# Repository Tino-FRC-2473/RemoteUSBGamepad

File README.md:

# RemoteUSBGamepad

Bridge USB gamepads over IP to enable FTC remote operation

# Client
Download the <a href="https://raw.githubusercontent.com/Tino-FRC-2473/RemoteUSBGamepad/master/client/controller_client.html" download>client page</a> (right click -> Save As) and open in a browser.  The client webpage uses the [Javascript Gamepad API](https://developer.mozilla.org/en-US/docs/Web/API/Gamepad_API), which is sufficiently supported by most modern browsers. 

1. Enter the address and port of the server you wish to connect to.

2. Then connect a gamepad to your computer and press some buttons so the browser can detect it. If you are using the Logitech F310 controller, make sure the switch on the back is set to "D" before plugging it into your computer.

3. Press the Connect button to establish connection to the server

# Server
This project uses pipenv to manage dependencies. Run `pipenv install` on first clone to download and install Python dependencies.

Run server script with `pipenv run python3 server/gamepad_bridge_server.py /dev/serial0`, replacing `/dev/serial0` with the appropriate serial UART for your system. For testing, you can add the `--dummy-serial` option to skip connecting to a physical serial port.

# Firmware
The firmware is written to run on both [Teensy boards](https://www.pjrc.com/teensy/) via the [Teensyduino Joystick API](https://www.pjrc.com/teensy/td_joystick.html) and Arduino boards via the [Arduino XInput library](https://github.com/dmadison/ArduinoXInput). Note that the XInput library requires additional installation procedures, but can run on either Arduino or Teensy boards. Also, XInput is a Microsoft API, so boards running with the XInput library will not be detected as joysticks on Mac or Linux computers without additional software. On an Android phone running the driver station app, XInput devices will appear as Xbox 360 controllers.

# Teensy Carrier Board

The Teensys listen for incoming command on a common serial bus. To simplify connecting all the RX lines together to the Raspberry Pi's serial TX, we designed a simple carrier board. The first design is a single-sided prototype suitable for milling on a desktop CNC machine. Each board holds four Teensy LCs, with headers for ground and serial RX. Note that the Teensys receive power via USB, but share a common ground with the Raspberry Pi. A second set of headers allows these boards to be daisy chained to easily add additional Teensys. The address or device index for each Teensy is programmed using a set of jumpers selective pulling down GPIO pins 2-5. Each Teensy reads its ID as a binary coded number on boot based on the jumper configuration.

# Protocol
The same binary message format will be used over the Websocket and serial connection. We shall use little-endian byte order to match the Arduino/ARM processor convention. All messages start with the following header:

Field | Size (bytes) | Description 
------------ | ------------- | -------------
Index | 1 | ID of destination controller
Command ID | 1 | Numeric identifier signfying message type
Length | 2 | Length of the message body in bytes. Note this does not include this header, only the contents following.

## Connection Start Command (CID=0x00)
Signify that a client has connected to the given controller index. No message body (length = 0).

## Connection End Command (CID=0x01)
Signify that a client has disconnected from the given controller index. No message body (length = 0).

## Controller State Report (CID=0x80)
Report the controller state from client to server/device. Message body:

Field | Size (bytes) | Description 
------------ | ------------- | -------------
Joystick1_X | 2 | Joystick 1 X Axis value. Format as 16 bit signed integer.
Joystick1_Y | 2 | Joystick 1 Y Axis value
Joystick2_X | 2 | Joystick 2 X Axis value
Joystick2_Y | 2 | Joystick 2 Y Axis value
Button_state | 2 | Bitfield indicating status of controller buttons. Bit(x) = 1 if pressed, 0 if unpressed. Bits counted from LSB.
RESERVED | 2 | Unused, space reserved for padding to 4b alignment.

## XInput Controller State Report (CID=0x81)
Report a Windows XInput controller state from client to server/device. Message body:

Field | Size (bytes) | Description 
------------ | ------------- | -------------
Joystick1_X | 2 | Joystick 1 X Axis value. Format as 16 bit signed integer.
Joystick1_Y | 2 | Joystick 1 Y Axis value
Joystick2_X | 2 | Joystick 2 X Axis value
Joystick2_Y | 2 | Joystick 2 Y Axis value
Button_state | 2 | Bitfield indicating status of controller buttons. Bit(x) = 1 if pressed, 0 if unpressed. Bits counted from LSB.
Trigger_L | 1 | Trigger value, format as 8 bit unsigned integer
Trigger_R | 1 | Trigger value, format as 8 bit unsigned integer

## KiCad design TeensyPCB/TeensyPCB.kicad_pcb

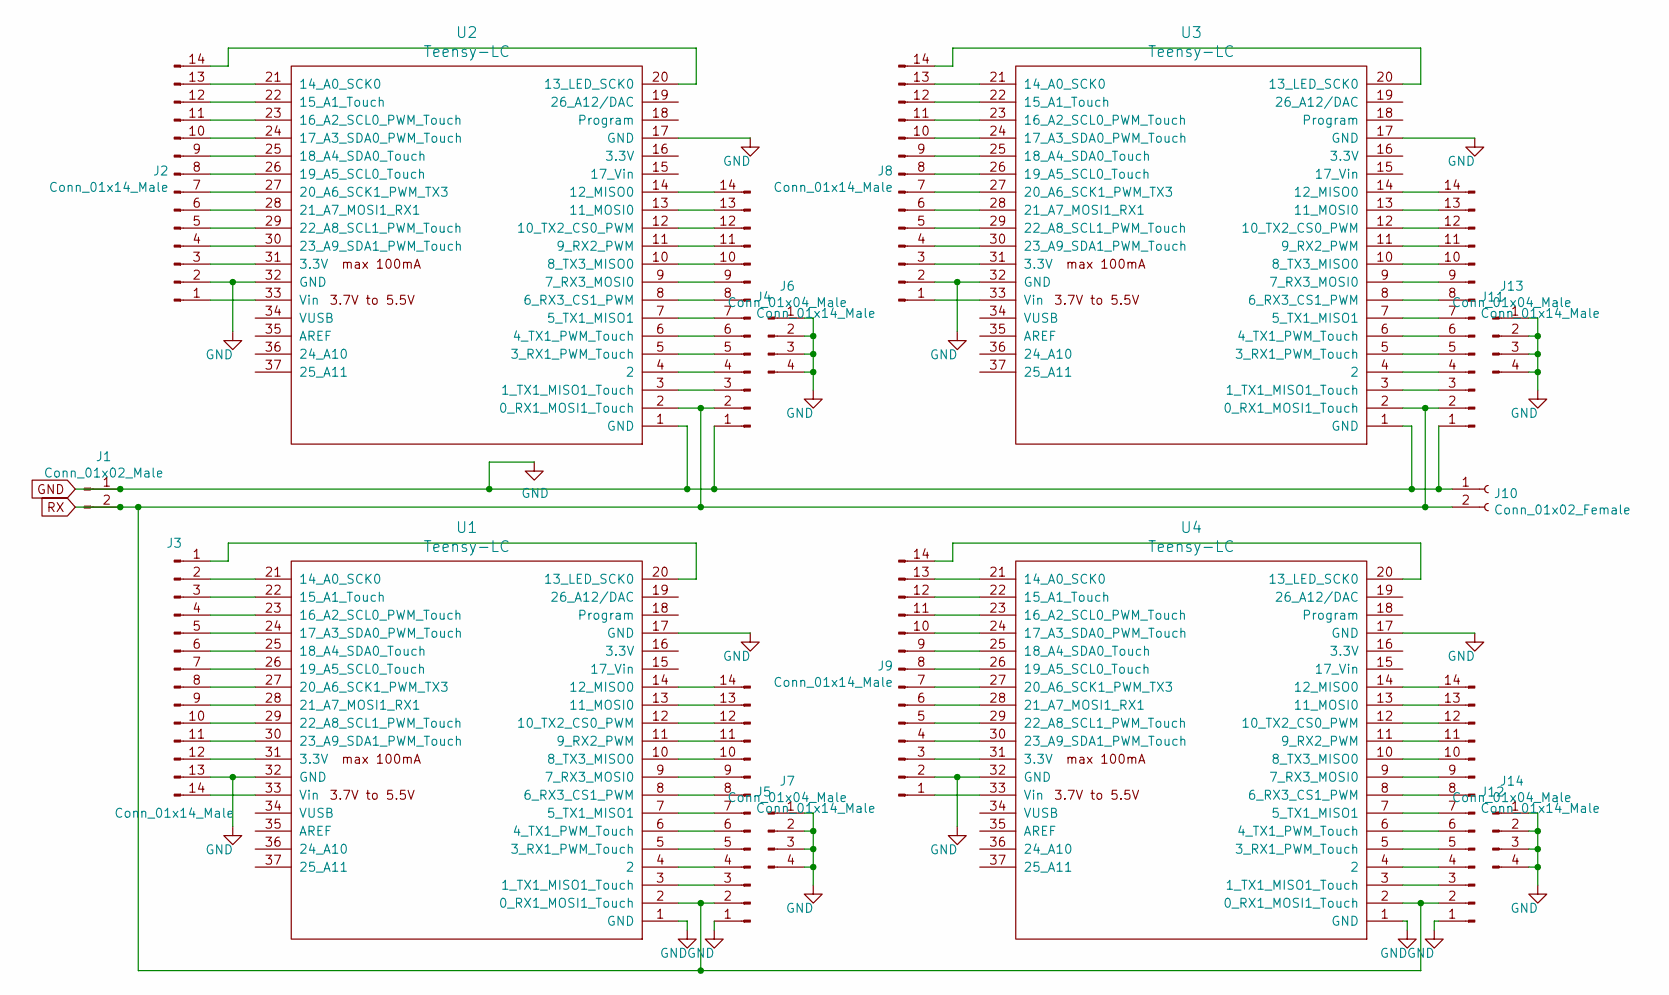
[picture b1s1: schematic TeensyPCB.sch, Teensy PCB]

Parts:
J1: Conn_01x02_Male; PinHeader_1x02_P2.54mm_Vertical
J2, J3, J4, J5, J8, J9, J11, J12: Conn_01x14_Male; PinHeader_1x14_P2.54mm_Vertical
J6, J7, J13, J14: Conn_01x04_Male; PinHeader_1x04_P2.54mm_Vertical
J10: Conn_01x02_Female; PinHeader_1x02_P2.54mm_Vertical
U1, U2, U3, U4: Teensy-LC; Teensy30_31_32_LC_nopogo

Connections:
GND: J1.1, J2.2, J3.13, J4.1, J5.1, J6.1, J6.2, J6.3, J6.4, J7.1, J7.2, J7.3, J7.4, J8.2, J9.2, J10.1, J11.1, J12.1, J13.1, J13.2, J13.3, J13.4, J14.1, J14.2, J14.3, J14.4, U1.1 (GND), U1.17 (GND), U1.32 (GND), U2.1 (GND), U2.17 (GND), U2.32 (GND), U3.1 (GND), U3.17 (GND), U3.32 (GND), U4.1 (GND), U4.17 (GND), U4.32 (GND)
unnamed: J2.1, U2.33 (Vin)
unnamed: J2.3, U2.31 (3.3V)
unnamed: J2.4, U2.30 (23_A9_SDA1_PWM_Touch)
unnamed: J2.5, U2.29 (22_A8_SCL1_PWM_Touch)
unnamed: J2.6, U2.28 (21_A7_MOSI1_RX1)
unnamed: J2.7, U2.27 (20_A6_SCK1_PWM_TX3)
unnamed: J2.8, U2.26 (19_A5_SCL0_Touch)
unnamed: J2.9, U2.25 (18_A4_SDA0_Touch)
unnamed: J2.10, U2.24 (17_A3_SDA0_PWM_Touch)
unnamed: J2.11, U2.23 (16_A2_SCL0_PWM_Touch)
unnamed: J2.12, U2.22 (15_A1_Touch)
unnamed: J2.13, U2.21 (14_A0_SCK0)
unnamed: J2.14, U2.20 (13_LED_SCK0)
unnamed: J3.1, U1.20 (13_LED_SCK0)
unnamed: J3.2, U1.21 (14_A0_SCK0)
unnamed: J3.3, U1.22 (15_A1_Touch)
unnamed: J3.4, U1.23 (16_A2_SCL0_PWM_Touch)
unnamed: J3.5, U1.24 (17_A3_SDA0_PWM_Touch)
unnamed: J3.6, U1.25 (18_A4_SDA0_Touch)
unnamed: J3.7, U1.26 (19_A5_SCL0_Touch)
unnamed: J3.8, U1.27 (20_A6_SCK1_PWM_TX3)
unnamed: J3.9, U1.28 (21_A7_MOSI1_RX1)
unnamed: J3.10, U1.29 (22_A8_SCL1_PWM_Touch)
unnamed: J3.11, U1.30 (23_A9_SDA1_PWM_Touch)
unnamed: J3.12, U1.31 (3.3V)
unnamed: J3.14, U1.33 (Vin)
unnamed: J4.3, U2.3 (1_TX1_MISO1_Touch)
unnamed: J4.4, U2.4 (2)
unnamed: J4.5, U2.5 (3_RX1_PWM_Touch)
unnamed: J4.6, U2.6 (4_TX1_PWM_Touch)
unnamed: J4.7, U2.7 (5_TX1_MISO1)
unnamed: J4.8, U2.8 (6_RX3_CS1_PWM)
unnamed: J4.9, U2.9 (7_RX3_MOSI0)
unnamed: J4.10, U2.10 (8_TX3_MISO0)
unnamed: J4.11, U2.11 (9_RX2_PWM)
unnamed: J4.12, U2.12 (10_TX2_CS0_PWM)
unnamed: J4.13, U2.13 (11_MOSI0)
unnamed: J4.14, U2.14 (12_MISO0)
unnamed: J5.3, U1.3 (1_TX1_MISO1_Touch)
unnamed: J5.4, U1.4 (2)
unnamed: J5.5, U1.5 (3_RX1_PWM_Touch)
unnamed: J5.6, U1.6 (4_TX1_PWM_Touch)
unnamed: J5.7, U1.7 (5_TX1_MISO1)
unnamed: J5.8, U1.8 (6_RX3_CS1_PWM)
unnamed: J5.9, U1.9 (7_RX3_MOSI0)
unnamed: J5.10, U1.10 (8_TX3_MISO0)
unnamed: J5.11, U1.11 (9_RX2_PWM)
unnamed: J5.12, U1.12 (10_TX2_CS0_PWM)
unnamed: J5.13, U1.13 (11_MOSI0)
unnamed: J5.14, U1.14 (12_MISO0)
unnamed: J8.1, U3.33 (Vin)
unnamed: J8.3, U3.31 (3.3V)
unnamed: J8.4, U3.30 (23_A9_SDA1_PWM_Touch)
unnamed: J8.5, U3.29 (22_A8_SCL1_PWM_Touch)
unnamed: J8.6, U3.28 (21_A7_MOSI1_RX1)
unnamed: J8.7, U3.27 (20_A6_SCK1_PWM_TX3)
unnamed: J8.8, U3.26 (19_A5_SCL0_Touch)
unnamed: J8.9, U3.25 (18_A4_SDA0_Touch)
unnamed: J8.10, U3.24 (17_A3_SDA0_PWM_Touch)
unnamed: J8.11, U3.23 (16_A2_SCL0_PWM_Touch)
unnamed: J8.12, U3.22 (15_A1_Touch)
unnamed: J8.13, U3.21 (14_A0_SCK0)
unnamed: J8.14, U3.20 (13_LED_SCK0)
unnamed: J9.1, U4.33 (Vin)
unnamed: J9.3, U4.31 (3.3V)
unnamed: J9.4, U4.30 (23_A9_SDA1_PWM_Touch)
unnamed: J9.5, U4.29 (22_A8_SCL1_PWM_Touch)
unnamed: J9.6, U4.28 (21_A7_MOSI1_RX1)
unnamed: J9.7, U4.27 (20_A6_SCK1_PWM_TX3)
unnamed: J9.8, U4.26 (19_A5_SCL0_Touch)
unnamed: J9.9, U4.25 (18_A4_SDA0_Touch)
unnamed: J9.10, U4.24 (17_A3_SDA0_PWM_Touch)
unnamed: J9.11, U4.23 (16_A2_SCL0_PWM_Touch)
unnamed: J9.12, U4.22 (15_A1_Touch)
unnamed: J9.13, U4.21 (14_A0_SCK0)
unnamed: J9.14, U4.20 (13_LED_SCK0)
unnamed: J11.3, U3.3 (1_TX1_MISO1_Touch)
unnamed: J11.4, U3.4 (2)
unnamed: J11.5, U3.5 (3_RX1_PWM_Touch)
unnamed: J11.6, U3.6 (4_TX1_PWM_Touch)
unnamed: J11.7, U3.7 (5_TX1_MISO1)
unnamed: J11.8, U3.8 (6_RX3_CS1_PWM)
unnamed: J11.9, U3.9 (7_RX3_MOSI0)
unnamed: J11.10, U3.10 (8_TX3_MISO0)
unnamed: J11.11, U3.11 (9_RX2_PWM)
unnamed: J11.12, U3.12 (10_TX2_CS0_PWM)
unnamed: J11.13, U3.13 (11_MOSI0)
unnamed: J11.14, U3.14 (12_MISO0)
unnamed: J12.3, U4.3 (1_TX1_MISO1_Touch)
unnamed: J12.4, U4.4 (2)
unnamed: J12.5, U4.5 (3_RX1_PWM_Touch)
unnamed: J12.6, U4.6 (4_TX1_PWM_Touch)
unnamed: J12.7, U4.7 (5_TX1_MISO1)
unnamed: J12.8, U4.8 (6_RX3_CS1_PWM)
unnamed: J12.9, U4.9 (7_RX3_MOSI0)
unnamed: J12.10, U4.10 (8_TX3_MISO0)
unnamed: J12.11, U4.11 (9_RX2_PWM)
unnamed: J12.12, U4.12 (10_TX2_CS0_PWM)
unnamed: J12.13, U4.13 (11_MOSI0)
unnamed: J12.14, U4.14 (12_MISO0)
RX: J1.2, J4.2, J5.2, J10.2, J11.2, J12.2, U1.2 (0_RX1_MOSI1_Touch), U2.2 (0_RX1_MOSI1_Touch), U3.2 (0_RX1_MOSI1_Touch), U4.2 (0_RX1_MOSI1_Touch)

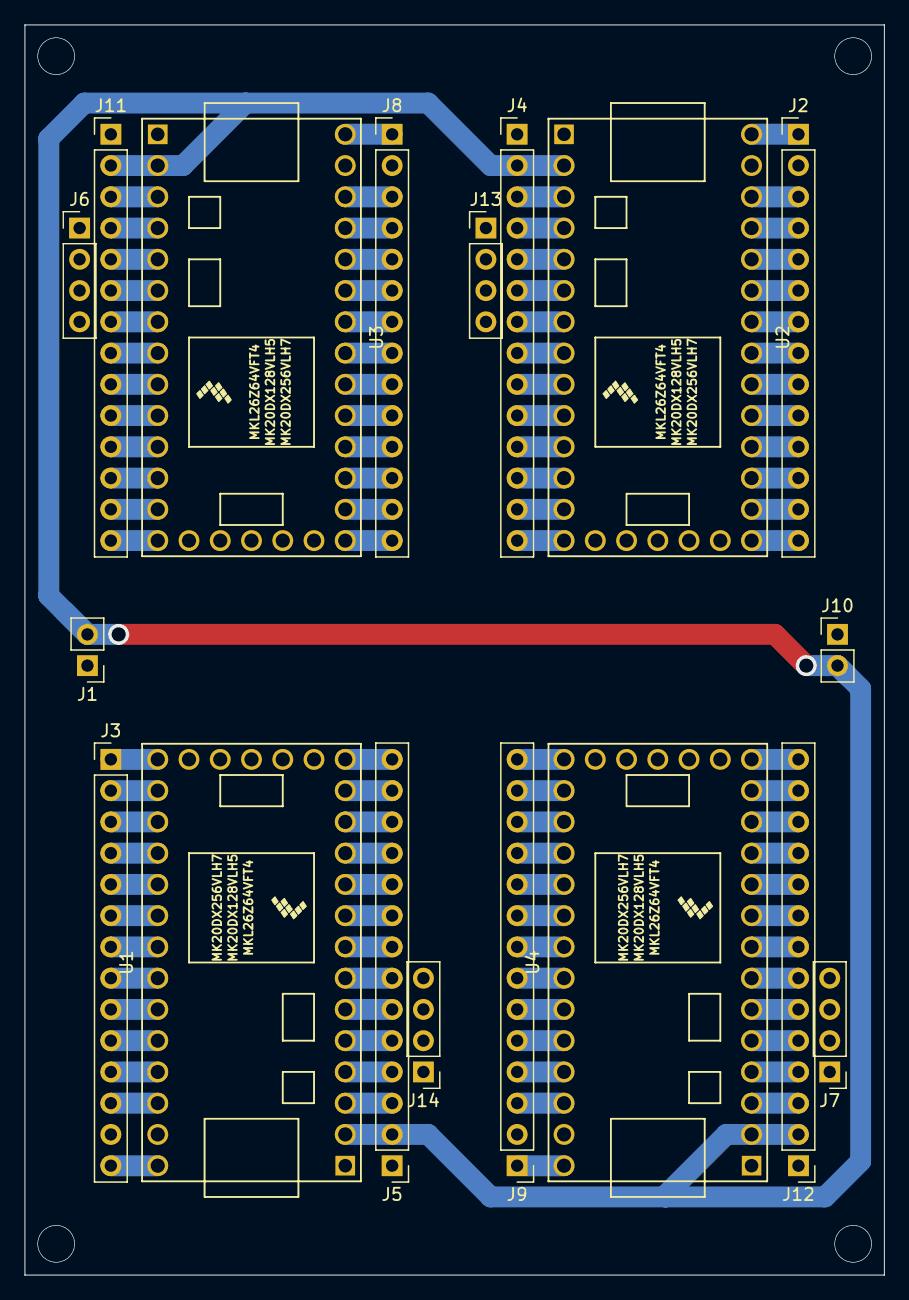
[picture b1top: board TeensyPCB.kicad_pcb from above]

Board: 2 copper layers, 69.8 x 101.6 mm, 18 parts (0 on the bottom side), 102 nets.

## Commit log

2020-07-17 Initial websocket client/server experiments
2020-07-18 Update readme with protocol spec
2020-07-18 Implement status report over websocket
2020-07-18 Get the right serial package
2020-07-23 Add serial output to server
2020-07-23 Modify client to prompt for server address
2020-07-24 Add firmware for Teensy performing USB emulation
2020-07-25 Add debug serial logging
2020-07-26 Add more buttons to client
2020-07-30 Add gamepad support
2020-07-30 Autocalculate index from socket URL
2020-08-01 Tidy up firmware comments
2020-08-01 Add Arduino XInput support
    Add firmware code to support using the Arduino XInput library.
    This allows certain non-Teensy Arduino boards to be used. In
    addition, make protocol spec updates to begin support for
    XInput controllers. In particular, analog trigger values.
2020-08-01 Fix XInput button map
2020-08-01 Update README with more detailed instructions
2020-08-01 Update server instructions in README
2020-08-10 Added Teensy PCB
2020-08-10 Mess up with git, moved PCB into correct folder.
2020-08-11 Add Kicad files to gitignore
2020-08-11 Remove pogo pins from Teensy footprint
    Simplify the Teensy footprints by removing unused test point pogos.
    Also introduce a via/jumper to greatly reduce the amount of ground
    plane division.
2020-08-11 Relocate symbols/footprints to local library
    Non-standard symbols and footprints for the Teensy are relocated
    to a project-local library under libraries directory. This ensures
    portability and allows modification without interfering with
    standard libraries.
2020-08-14 Added headers to ground pins on the board
2020-08-14 Fix symbol library path
2020-08-14 Break out rest of GPIO pins
    Break out all GPIO pins on all Teensys. Also make a few footprint edits:
    - Increase hole size to 1.15mm
    - Delete inner holes on Teensy footprint
2020-08-14 General cleanup and optimization for milling
    Realign boards for more centered layout. Also increase track size to
    match via diameter for smoother milling and add 4-40 mounting holes.
    RX lines also sligtly rereouted to avoid creating hanging ground
    around the headers for board ID selection.
2020-08-17 Handle unexpected connection termination
    When the server receives an unexpected websocket termination, send
    a disconnect message to the corresponding Teensy over serial.
2020-09-05 Add PCB outputs for v1 board
2020-09-05 Add PCB PDF exports
2020-09-07 Enable reading multiple bit index
2020-09-08 Add client github.io link to readme
2020-09-19 Fix controller disconnecting on server disconnect
2020-10-05 Add ping calculation to client
2020-10-05 Add client screenshots
2020-10-07 Improve server logging
2020-10-07 Update cert generation
2020-10-07 Convert to HTTPS
2020-11-01 Add version of carrier PCB for OshPark
2020-11-01 Adjust board size to fit within 100mm
2020-11-01 Optimizations for better clearances and DRC
2020-11-01 Add gerber export for first fab run
2020-11-01 Add PDF export
2020-11-03 Relax Pipfile Python version requirement
    While websockets does specify a minimum Python version of 3.6.1,
    Pipfile requires strict matching of Python version. Relax to only
    check for Python 3 to avoid conflicts.
2020-11-06 Rename fab board files to generic naming
2020-11-06 Untrack source images for block diagram
2020-11-06 Update gitignore
2020-11-10 Add systemd service config
    Install systemd service called remoteusbserver.service to allow
    automatic launching of the server on reboot and unified logging.
2020-11-10 Add setup step to set timezone
2020-11-26 Add enhanced debug options to client
2020-11-26 Add message counters
